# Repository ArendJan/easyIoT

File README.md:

# EasyIoT
Follow [the tutorial](./tutorial.md) for how to install and use.

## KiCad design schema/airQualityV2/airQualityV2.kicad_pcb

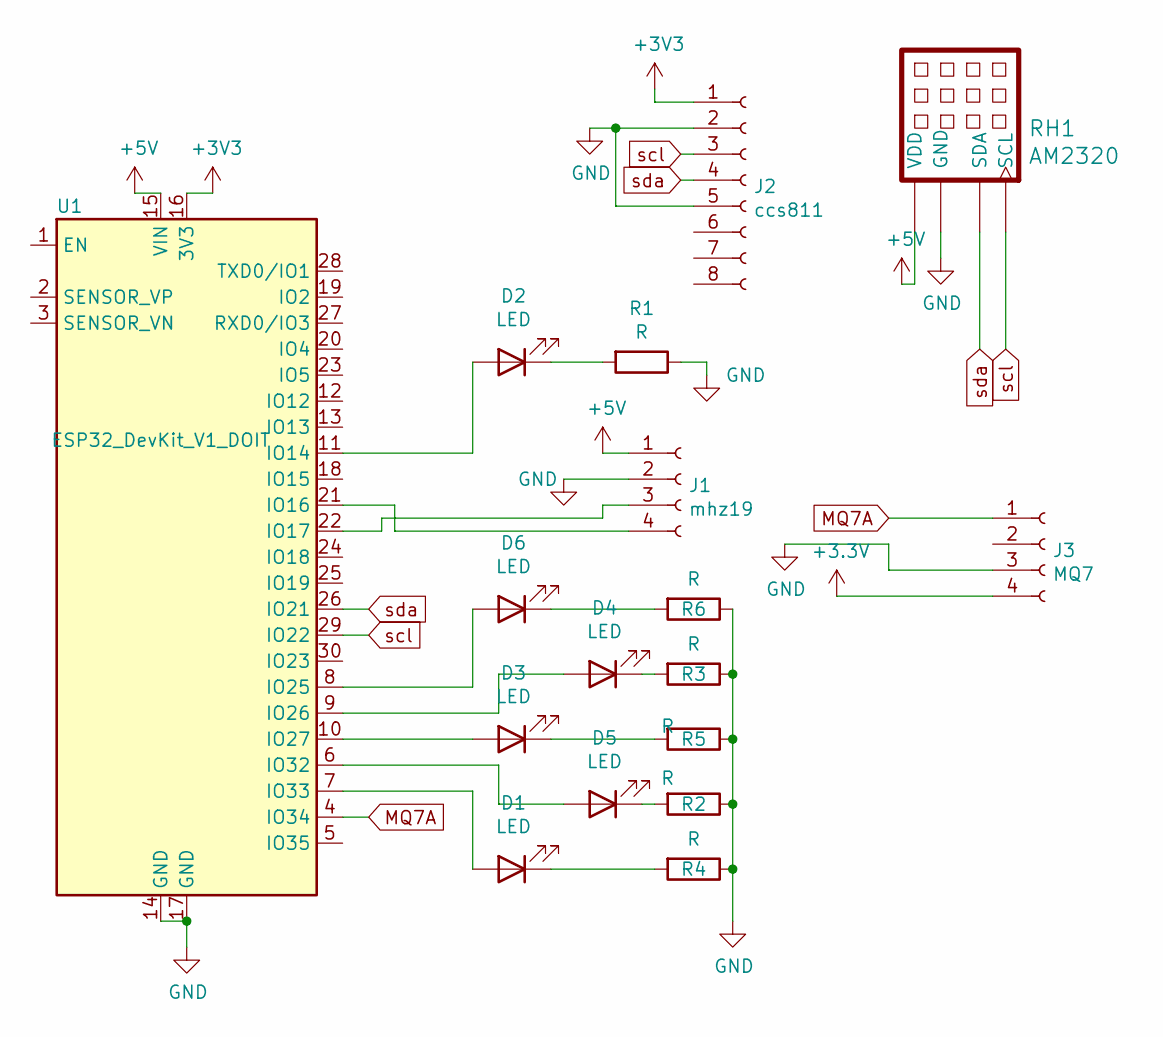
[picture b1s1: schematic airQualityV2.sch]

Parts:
D1, D2, D3, D4, D5, D6: LED; LED_D3.0mm
J1: mhz19; PinHeader_1x04_P2.54mm_Vertical
J2: ccs811; PinHeader_1x08_P2.54mm_Vertical
J3: MQ7; PinSocket_1x04_P2.54mm_Vertical
R1, R2, R3, R4, R5, R6: R; R_Axial_DIN0204_L3.6mm_D1.6mm_P5.08mm_Vertical
RH1: AM2320
U1: ESP32_DevKit_V1_DOIT; esp32_devkit_v1_doit

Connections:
+5V: J1.1, RH1.1 (VDD), U1.15 (VIN)
GND: J1.2, J2.2, J2.5, J3.3, R1.1, R2.1, R3.1, R4.1, R5.1, R6.1, RH1.3 (GND), U1.14 (GND), U1.17 (GND)
MQ7A: J3.1, U1.4 (IO34)
unnamed: D1.1 (K), R4.2
unnamed: D1.2 (A), U1.7 (IO33)
unnamed: D2.1 (K), R1.2
unnamed: D2.2 (A), U1.11 (IO14)
unnamed: D3.1 (K), R5.2
unnamed: D3.2 (A), U1.10 (IO27)
unnamed: D4.1 (K), R3.2
unnamed: D4.2 (A), U1.9 (IO26)
unnamed: D5.1 (K), R2.2
unnamed: D5.2 (A), U1.6 (IO32)
unnamed: D6.1 (K), R6.2
unnamed: D6.2 (A), U1.8 (IO25)
unnamed: J1.3, U1.22 (IO17)
unnamed: J1.4, U1.21 (IO16)
scl: J2.3, RH1.4 (SCL), U1.29 (IO22)
sda: J2.4, RH1.2 (SDA), U1.26 (IO21)

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
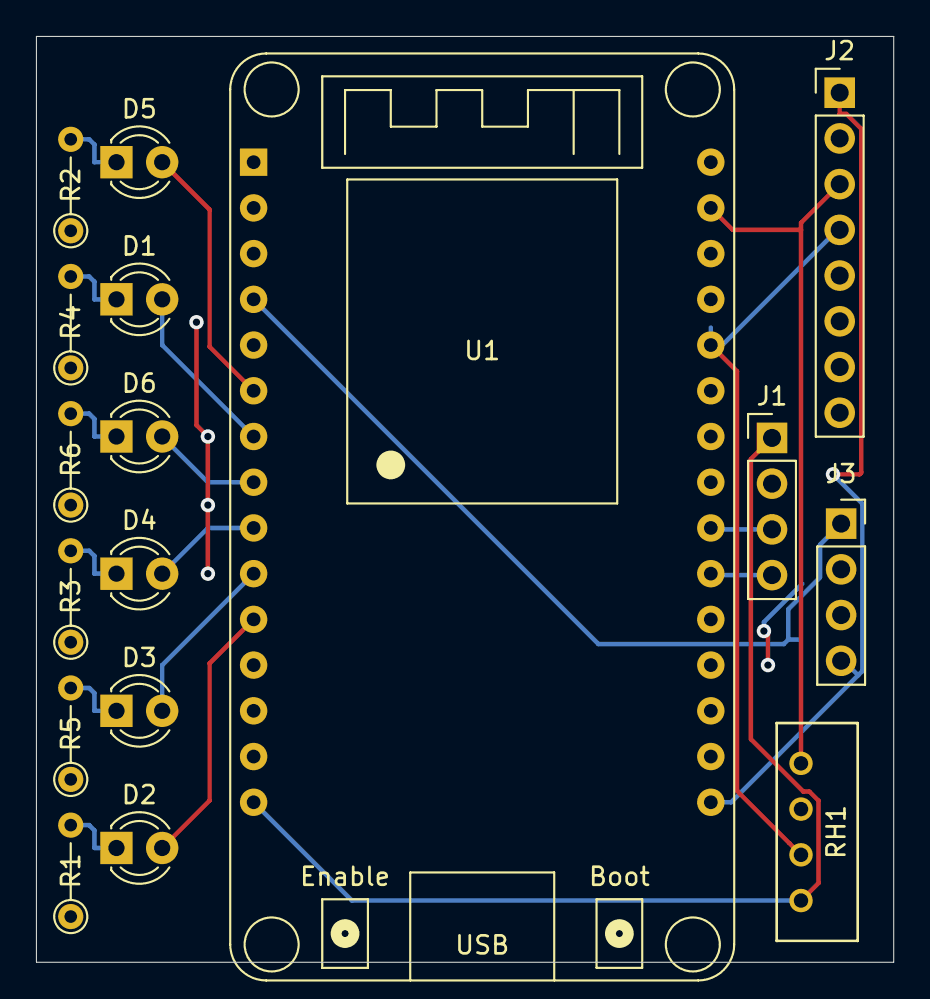
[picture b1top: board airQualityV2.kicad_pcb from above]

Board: 2 copper layers, 47.6 x 51.4 mm, 17 parts (0 on the bottom side), 20 nets.

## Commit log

2021-11-17 easyIoT copy code without passwords!
2021-11-17 Add tutorial
2021-11-17 Add tutorial link
2021-11-17 change old names
2021-11-23 update schematic
2021-11-23 update analyzers
2021-11-30 Add report
